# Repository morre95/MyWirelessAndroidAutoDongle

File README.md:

# Wireless Android Auto Dongle

DIY Wireless Android Auto adapter to use with a car that supports only wired Android Auto using a Raspberry Pi.

This repository consists of the buildroot setup to generate an sd card image to create your own Wireless Android Auto adapter.

## Features
- Native Wireless Android Auto connection to the phone, no extra app needed on the phone.
- Passes through all Android Auto traffic without any modifications to ensure seamless and safe experience.
- Fast bootup, connection under 30 seconds.
- Supports multiple boards (Currently multiple Raspberry Pi boards and the Radxa ZERO 3W).

## Supported Hardware
This is currently tested and built for the following boards supporting USB OTG.
- **Raspberry Pi Zero W**
- **Raspberry Pi Zero 2 W**
- **Raspberry Pi 3 A+** _(Raspberry Pi 3 B+ is not supported due to lack of USB OTG support.)_
- **Raspberry Pi 4**
- **Raspberry Pi 5**
- **Radxa ZERO 3W**: only the tested variant (PCB V1.12M, 1 GB RAM, **no eMMC**, AIC8800D80 radio), booting from microSD. Variants with eMMC or another revision are not supported. First released in [v0.2.0](https://github.com/morre95/MyWirelessAndroidAutoDongle/releases/tag/v0.2.0); see [Limitations](#radxa-zero-3w).

In theory, this can be extended to more hardware in future with these basic requirements.

- The board should support USB OTG or Gadget mode.
- Has Wifi and Bluetooth. External should also work if not in-built.
- Should be able to operate on power provided by the car.

## Install and run
[Download a pre-built sd card image](https://github.com/morre95/MyWirelessAndroidAutoDongle/releases) for your board. You can also [build one yourself](BUILDING.md). Install the image on the SD card using your favorite tool.

Release images are named `<board>-sdcard.img.xz`, for example `radxa-zero3w-sdcard.img.xz`. Newer releases also carry a `.sha256` file next to each image. Download both into the same folder and check the image before flashing:

```shell
sha256sum -c radxa-zero3w-sdcard.img.xz.sha256
```

Most imaging tools, such as Raspberry Pi Imager and balenaEtcher, can flash the `.img.xz` file directly. The image is about 386 MB, so any microSD card will fit it. The Radxa ZERO 3W was tested with a 32 GB SanDisk Ultra card.

You may want to update the country code and other settings that works best for you. See [Configurations](#Configurations)

### First-time connection
- Connect the phone to headunit via USB cable, make sure Android Auto starts. Disconnect phone.
- Connect the board to the car. Make sure to use a data cable, with the USB OTG enabled port on the board.
    - On **Raspberry Pi Zero W** and **Raspberry Pi Zero 2 W**: Use the second micro-usb port marked "USB" and not "PWR".
    - On **Raspberry Pi 3 A+**: Use the only USB-A port with an USB-A to USB-A cable.
    - On **Raspberry Pi 4**, use the USB-C port used for normally powering the board.
    - On **Radxa ZERO 3W**: Use USB-C port 1, the USB 2.0 OTG port that also powers the board, with a USB-C to USB-A data cable to the car. The other USB-C port is a USB 3.0 host port and does not power the board.
- Open Bluetooth settings and pair the new device called `AndroidAuto-Dongle-*` or `WirelessAADongle-*` on your phone.
- After this phone should automatically connect via Wifi and the dongle will connect to the headunit via USB and start Android Auto on the car screen.

### Subsequent connections
From the next time, it should automatically connect to the phone and start Android Auto.

Make sure your Bluetooth and Wifi are enabled on the phone.

## Configurations

Once the image is installed on the SD card, you can see the SD card as `WirelessAA` drive.

Edit the `aawgd.conf` file inside the `WirelessAA` drive using a text editor to update the configurations. The file contains the possible configuration options with their explanations.

The Radxa ZERO 3W runs its Wi-Fi access point on 5 GHz (channel 36); the Raspberry Pi boards use 2.4 GHz. Set `AAWG_COUNTRY_CODE` to the country you drive in.

## Troubleshoot

### Common issues

#### Music or audiobook playback stutters

See [the audio troubleshooting guide](AUDIO-TROUBLESHOOTING.md) for a reversible
TCP buffering comparison and instructions for collecting Wi-Fi/USB diagnostics.

#### Bluetooth and Wifi seems connected, but the phone stuck at "Looking for Android Auto"
The most common issue behind this is either bad USB cable or use of wrong USB port on the device. Make sure:
1. The cable is good quality data cable and not power-only cable
2. You're using the OTG enabled usb port on the board, and not the power-only port.

#### "Device not responding" error on headunit
Make sure that "Wireless Android Auto" is enabled in your phone's Andriod Auto settings. This option is only available and required on some older phones.

### Getting logs
Once you've already tried multiple times and it still does not work, you can ssh into the device and try to get some logs.

- Set a static password by setting the `AAWG_WIFI_PASSWORD` config, and enable SSH by setting the `AAWG_ENABLE_SSH` config. See [the instructions to update the configurations](#Configurations).
- Connect the device to the headunit, let it boot and try to connect once. The logs are not persisted across reboots, so you need to get the logs in the same instance soon after you observe the issue.
- Connect to the device using wifi (SSID: AAWirelessDongle, Password: \<as set in the first step>).
- SSH into the device (username: root, password: password, see relevant defconfigs e.g. [raspberrypi0w_defconfig](aa_wireless_dongle/configs/raspberrypi0w_defconfig)).
- Once you're in, try to have a look at `/var/log/messages` file, it should have most relevant logs to start with. You can also copy the file and attach to issues you create if any.

These steps are the same on the Radxa ZERO 3W, whose access point is on 5 GHz.

## Contribute
[Find or create a new issue](https://github.com/morre95/MyWirelessAndroidAutoDongle/issues) for any bugs or improvements.

Feel free to [Create a PR](https://github.com/morre95/MyWirelessAndroidAutoDongle/pulls) to fix any issues. Refer [BUILDING.md](BUILDING.md) for instructions on how to build locally.

## Support 
Please [consider sponsoring](https://github.com/sponsors/nisargjhaveri) if you find the project useful. Even a small donation helps. This will help continuing fixing issues and getting support for more devices and headunit in future.

In any case, don't forget to star on github and spread the word if you think this project might be useful to someone else as well.

## Limitations
This is currently tested with very limited set of headunits and cars. Let me know if it does not work with your headunit.

### Radxa ZERO 3W
The Radxa ZERO 3W has been tested with one board, one phone (Samsung Galaxy S24) and one car head unit. See the [hardware validation record](docs/hardware-validation/radxa-zero3w.md) for the results.
- From a fully switched-off car, Android Auto started in 21–27 seconds over 10 cold starts, including the head unit's own boot. A Raspberry Pi Zero 2 W in the same car took 16–24 seconds. An earlier series had one start at exactly 30 seconds.
- Only the variant listed under [Supported Hardware](#supported-hardware) is tested. Boards with eMMC are not supported.
- A 50-minute session with navigation and music had no disconnects. No logs were reviewed for it.

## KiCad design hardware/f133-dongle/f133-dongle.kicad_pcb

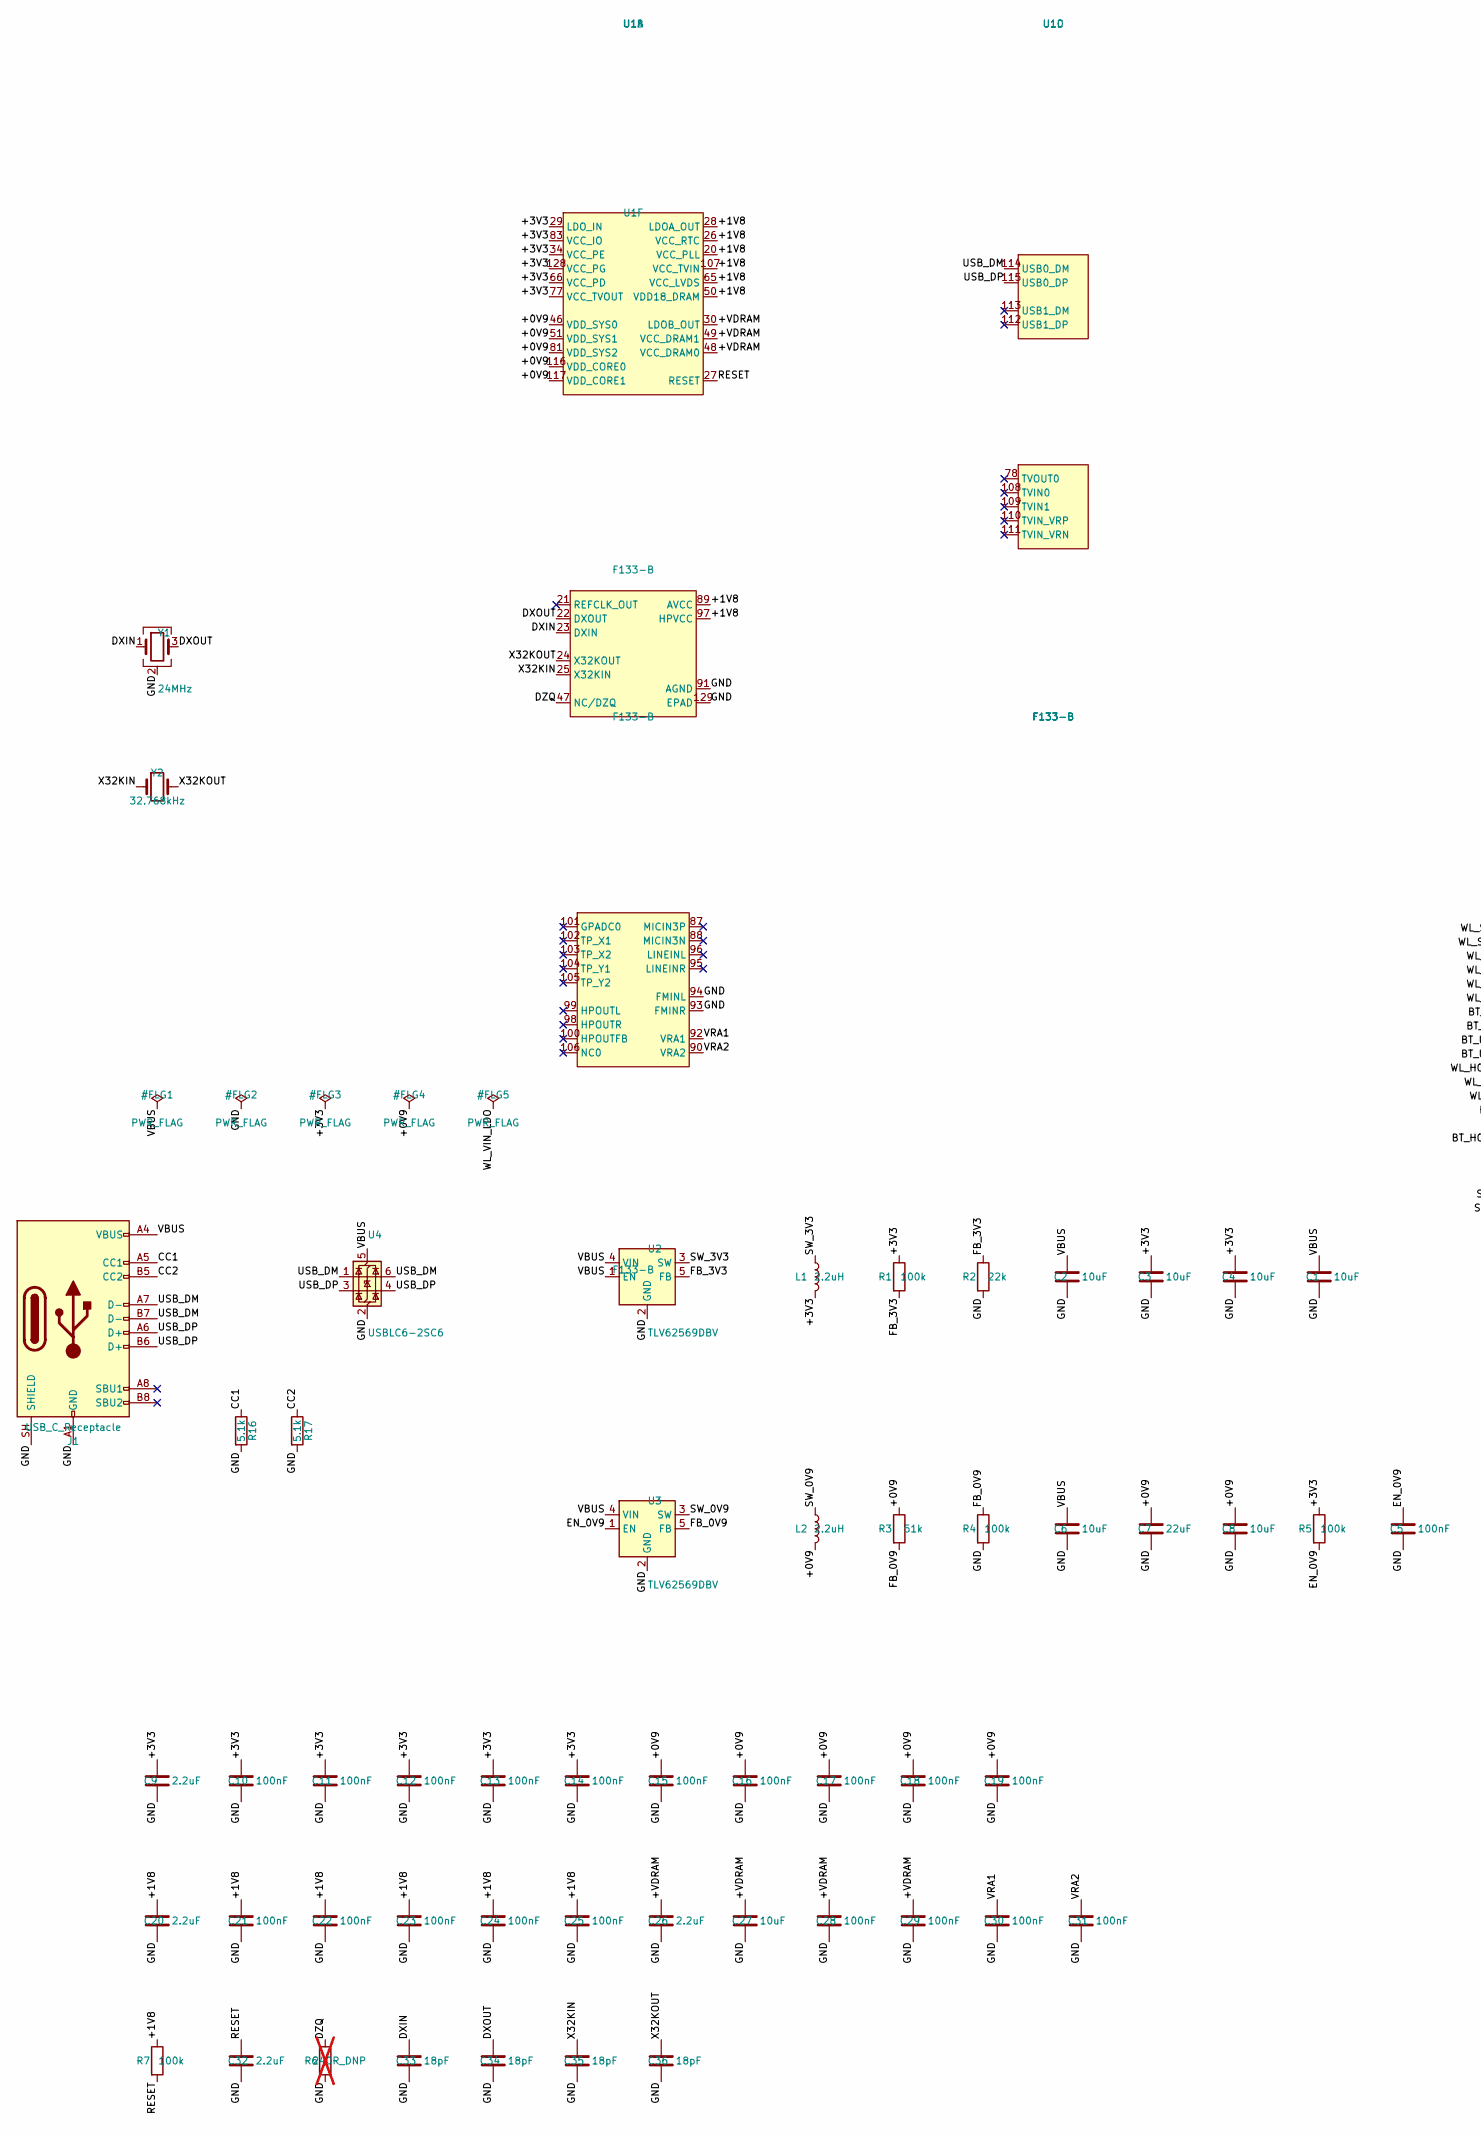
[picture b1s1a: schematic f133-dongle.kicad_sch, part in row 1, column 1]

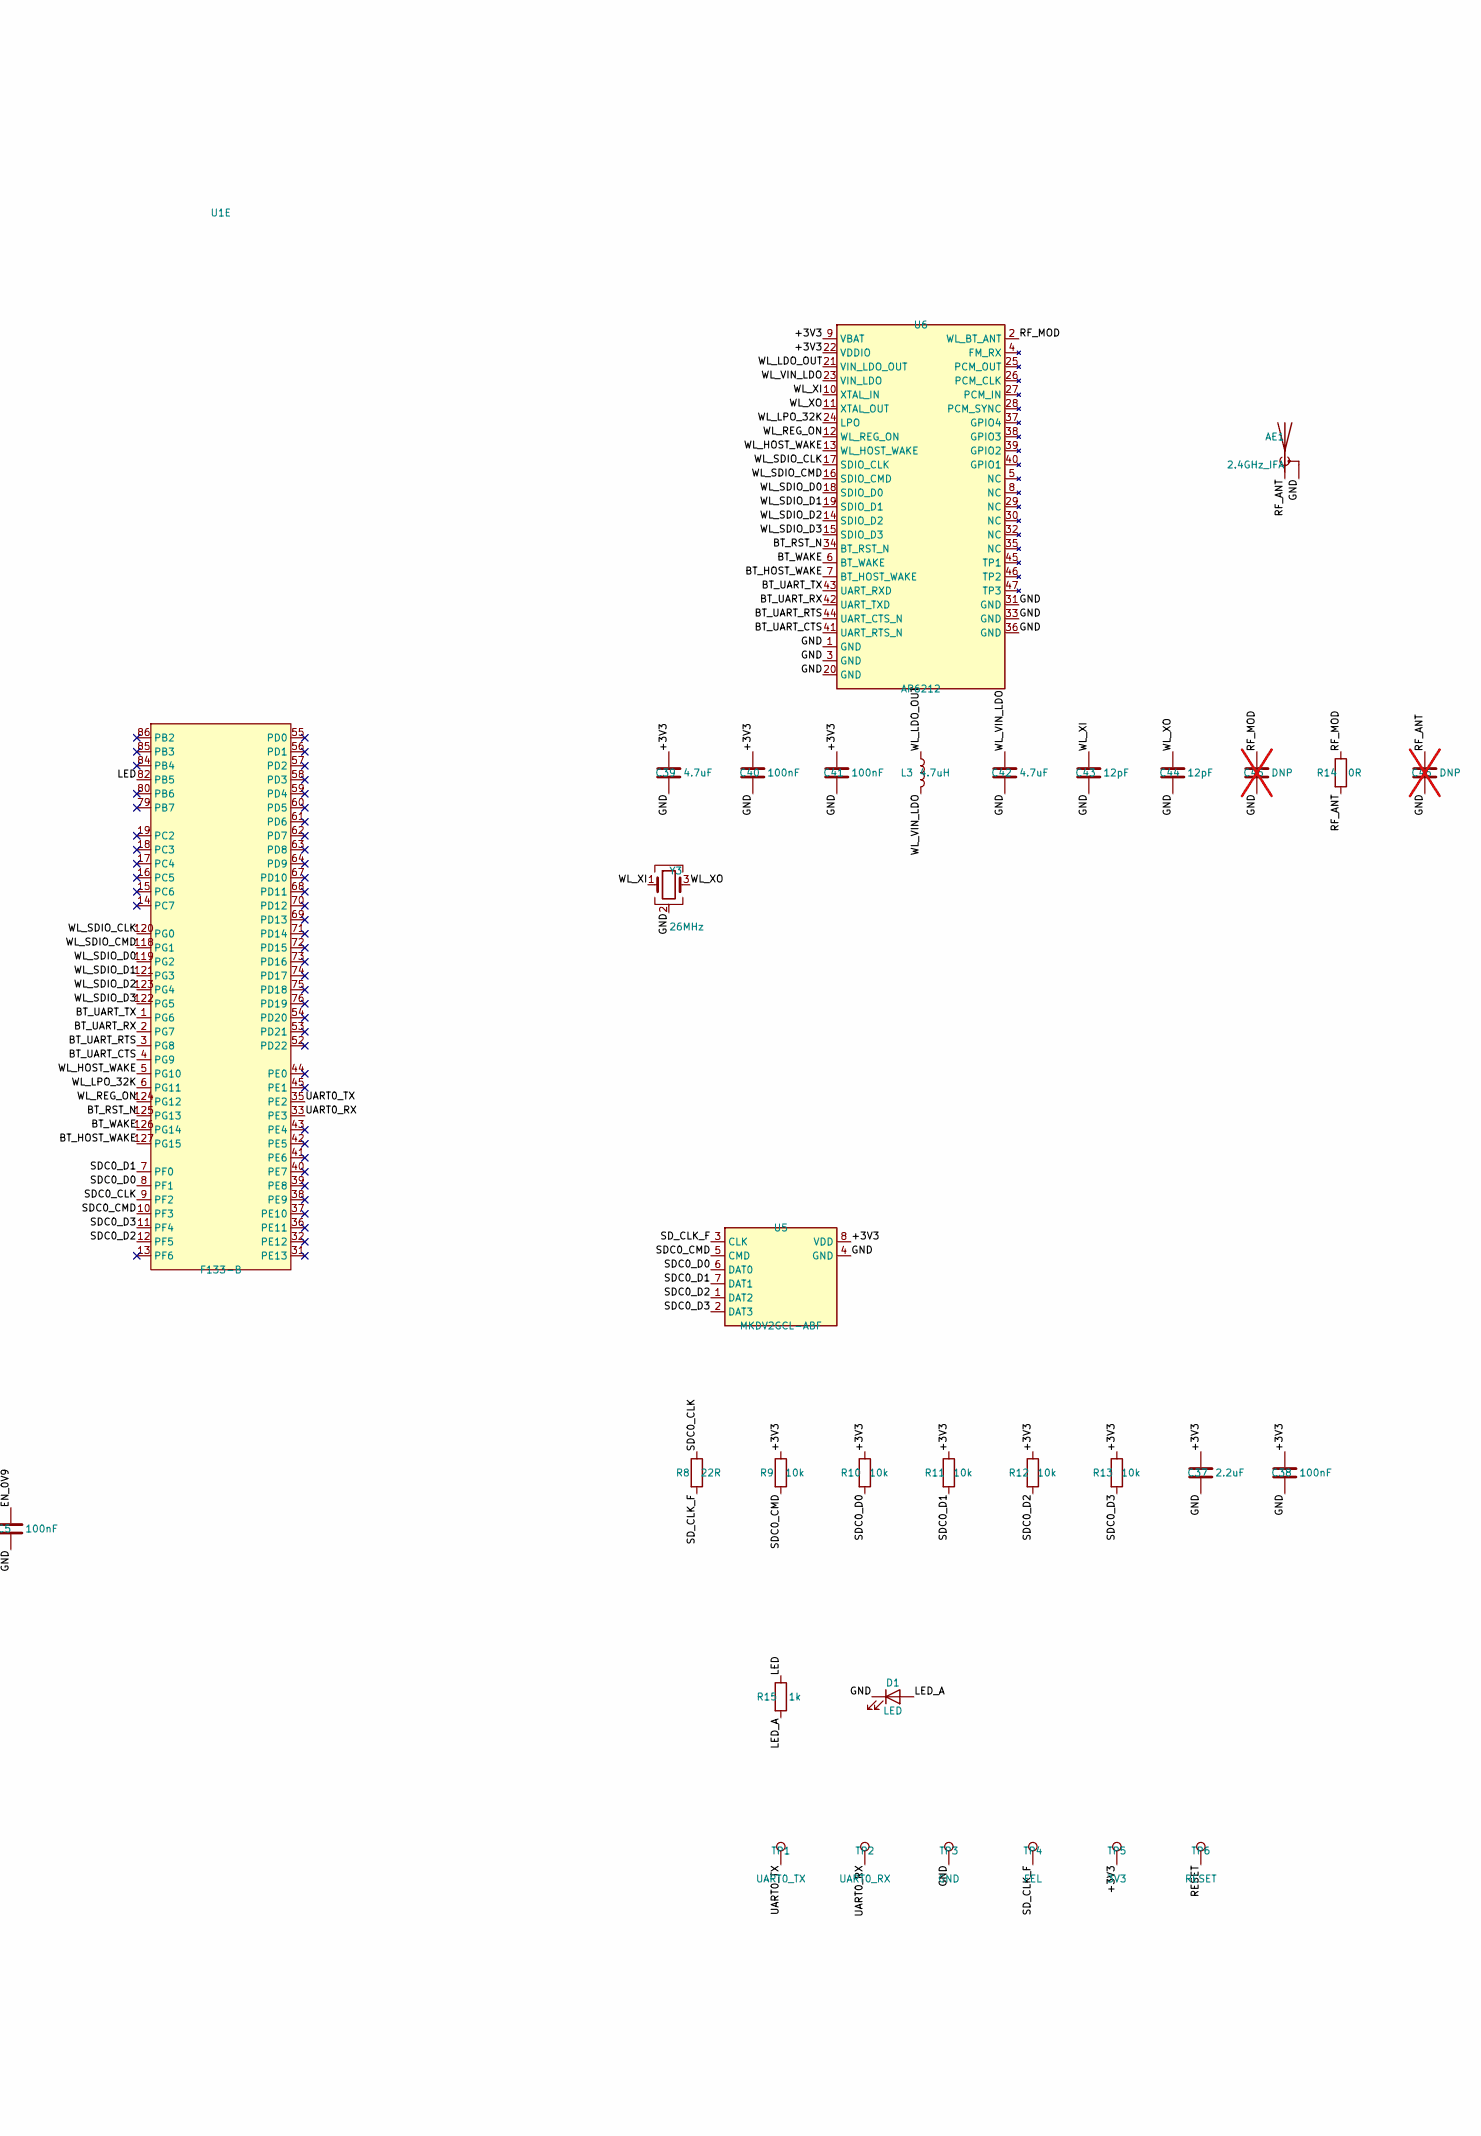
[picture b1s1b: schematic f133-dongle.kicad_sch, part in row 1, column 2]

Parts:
AE1: 2.4GHz_IFA; Texas_SWRA117D_2.4GHz_Left
C1, C2, C3, C4, C6, C8, C27: 10uF; C_0603_1608Metric; LCSC C96446
C5, C10, C11, C12, C13, C14, C15, C16, C17, C18, C19, C21, C22, C23, C24, C25, C28, C29, C30, C31, C38, C40, C41: 100nF; C_0402_1005Metric; LCSC C1525
C7: 22uF; C_0805_2012Metric; LCSC C45783
C9, C20, C26, C32, C37: 2.2uF; C_0402_1005Metric; LCSC C12530
C33, C34, C35, C36: 18pF; C_0402_1005Metric; LCSC C1549
C39, C42: 4.7uF; C_0603_1608Metric; LCSC C19666
C43, C44: 12pF; C_0402_1005Metric; LCSC C1547
C45, C46: DNP; C_0402_1005Metric; not fitted
D1: LED; LED_0603_1608Metric; LCSC C2286
J1: USB_C_Receptacle; USB_C_Receptacle_HRO_TYPE-C-31-M-12; LCSC C165948
L1, L2: 2.2uH; L_1008_2520Metric; LCSC C964122
L3: 4.7uH; L_0805_2012Metric; LCSC C86090
R1, R4, R5, R7: 100k; R_0402_1005Metric; LCSC C25741
R2: 22k; R_0402_1005Metric; LCSC C25768
R3: 51k; R_0402_1005Metric; LCSC C25794
R6: 240R_DNP; R_0402_1005Metric; LCSC C114755; not fitted
R8: 22R; R_0402_1005Metric; LCSC C25092
R9, R10, R11, R12, R13: 10k; R_0402_1005Metric; LCSC C25744
R14: 0R; R_0402_1005Metric; LCSC C17168
R15: 1k; R_0402_1005Metric; LCSC C11702
R16, R17: 5.1k; R_0402_1005Metric; LCSC C25905
TP1: UART0_TX; TestPoint_Pad_D1.0mm
TP2: UART0_RX; TestPoint_Pad_D1.0mm
TP3: GND; TestPoint_Pad_D1.0mm
TP4: FEL; TestPoint_Pad_D1.0mm
TP5: 3V3; TestPoint_Pad_D1.0mm
TP6: RESET; TestPoint_Pad_D1.0mm
U1: F133-B; eLQFP-128_14x14mm_P0.4mm_EP5.72mm; LCSC C22438485
U2, U3: TLV62569DBV; SOT-23-5; LCSC C141836
U4: USBLC6-2SC6; SOT-23-6; LCSC C7519
U5: MKDV2GCL-ABF; LGA-8_8x6mm_P1.27mm_SD_NAND; LCSC C51966231
U6: AP6212; AMPAK_AP62xx_12x12mm
Y1: 24MHz; Crystal_SMD_3225-4Pin_3.2x2.5mm; LCSC C164058
Y2: 32.768kHz; Crystal_SMD_3215-2Pin_3.2x1.5mm; LCSC C32346
Y3: 26MHz; Crystal_SMD_3225-4Pin_3.2x2.5mm; LCSC C15192

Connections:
/+0V9: C7.1, C8.1, C15.1, C16.1, C17.1, C18.1, C19.1, L2.2, R3.1, U1.46 (VDD_SYS0), U1.51 (VDD_SYS1), U1.81 (VDD_SYS2), U1.116 (VDD_CORE0), U1.117 (VDD_CORE1)
/+1V8: C20.1, C21.1, C22.1, C23.1, C24.1, C25.1, R7.1, U1.20 (VCC_PLL), U1.26 (VCC_RTC), U1.28 (LDOA_OUT), U1.50 (VDD18_DRAM), U1.65 (VCC_LVDS), U1.89 (AVCC), U1.97 (HPVCC), U1.107 (VCC_TVIN)
/+3V3: C3.1, C4.1, C9.1, C10.1, C11.1, C12.1, C13.1, C14.1, C37.1, C38.1, C39.1, C40.1, C41.1, L1.2, R1.1, R5.1, R9.1, R10.1, R11.1, R12.1, R13.1, TP5.1, U1.29 (LDO_IN), U1.34 (VCC_PE), U1.66 (VCC_PD), U1.77 (VCC_TVOUT), U1.83 (VCC_IO), U1.128 (VCC_PG), U5.8 (VDD), U6.9 (VBAT), U6.22 (VDDIO)
/+VDRAM: C26.1, C27.1, C28.1, C29.1, U1.30 (LDOB_OUT), U1.48 (VCC_DRAM0), U1.49 (VCC_DRAM1)
/BT_HOST_WAKE: U1.127 (PG15), U6.7 (BT_HOST_WAKE)
/BT_RST_N: U1.125 (PG13), U6.34 (BT_RST_N)
/BT_UART_CTS: U1.4 (PG9), U6.41 (UART_RTS_N)
/BT_UART_RTS: U1.3 (PG8), U6.44 (UART_CTS_N)
/BT_UART_RX: U1.2 (PG7), U6.42 (UART_TXD)
/BT_UART_TX: U1.1 (PG6), U6.43 (UART_RXD)
/BT_WAKE: U1.126 (PG14), U6.6 (BT_WAKE)
/CC1: J1.A5 (CC1), R16.1
/CC2: J1.B5 (CC2), R17.1
/DXIN: C33.1, U1.23 (DXIN), Y1.1
/DXOUT: C34.1, U1.22 (DXOUT), Y1.3
/DZQ: R6.1, U1.47 (NC/DZQ)
/EN_0V9: C5.1, R5.2, U3.1 (EN)
/FB_0V9: R3.2, R4.1, U3.5 (FB)
/FB_3V3: R1.2, R2.1, U2.5 (FB)
/GND: AE1.2 (Shield), C1.2, C2.2, C3.2, C4.2, C5.2, C6.2, C7.2, C8.2, C9.2, C10.2, C11.2, C12.2, C13.2, C14.2, C15.2, C16.2, C17.2, C18.2, C19.2, C20.2, C21.2, C22.2, C23.2, C24.2, C25.2, C26.2, C27.2, C28.2, C29.2, C30.2, C31.2, C32.2, C33.2, C34.2, C35.2, C36.2, C37.2, C38.2, C39.2, C40.2, C41.2, C42.2, C43.2, C44.2, C45.2, C46.2, D1.1 (K), J1.A1 (GND), J1.A12 (GND), J1.B1 (GND), J1.B12 (GND), J1.SH (SHIELD), R2.2, R4.2, R6.2, R16.2, R17.2, TP3.1, U1.91 (AGND), U1.93 (FMINR), U1.94 (FMINL), U1.129 (EPAD), U2.2 (GND), U3.2 (GND), U4.2 (GND), U5.4 (GND), U6.1 (GND), U6.3 (GND), U6.20 (GND), U6.31 (GND), U6.33 (GND), U6.36 (GND), Y1.2 (G), Y1.4 (G), Y3.2 (G), Y3.4 (G)
/LED: R15.1, U1.82 (PB5)
/LED_A: D1.2 (A), R15.2
/RESET: C32.1, R7.2, TP6.1, U1.27 (RESET)
/RF_ANT: AE1.1 (A), C46.1, R14.2
/RF_MOD: C45.1, R14.1, U6.2 (WL_BT_ANT)
/SDC0_CLK: R8.1, U1.9 (PF2)
/SDC0_CMD: R9.2, U1.10 (PF3), U5.5 (CMD)
/SDC0_D0: R10.2, U1.8 (PF1), U5.6 (DAT0)
/SDC0_D1: R11.2, U1.7 (PF0), U5.7 (DAT1)
/SDC0_D2: R12.2, U1.12 (PF5), U5.1 (DAT2)
/SDC0_D3: R13.2, U1.11 (PF4), U5.2 (DAT3)
/SD_CLK_F: R8.2, TP4.1, U5.3 (CLK)
/SW_0V9: L2.1, U3.3 (SW)
/SW_3V3: L1.1, U2.3 (SW)
/UART0_RX: TP2.1, U1.33 (PE3)
/UART0_TX: TP1.1, U1.35 (PE2)
/USB_DM: J1.A7 (D-), J1.B7 (D-), U1.114 (USB0_DM), U4.1 (I/O1), U4.6 (I/O1)
/USB_DP: J1.A6 (D+), J1.B6 (D+), U1.115 (USB0_DP), U4.3 (I/O2), U4.4 (I/O2)
/VBUS: C1.1, C2.1, C6.1, J1.A4 (VBUS), J1.A9 (VBUS), J1.B4 (VBUS), J1.B9 (VBUS), U2.1 (EN), U2.4 (VIN), U3.4 (VIN), U4.5 (VBUS)
/VRA1: C30.1, U1.92 (VRA1)
/VRA2: C31.1, U1.90 (VRA2)
/WL_HOST_WAKE: U1.5 (PG10), U6.13 (WL_HOST_WAKE)
/WL_LDO_OUT: L3.1, U6.21 (VIN_LDO_OUT)
/WL_LPO_32K: U1.6 (PG11), U6.24 (LPO)
/WL_REG_ON: U1.124 (PG12), U6.12 (WL_REG_ON)
/WL_SDIO_CLK: U1.120 (PG0), U6.17 (SDIO_CLK)
/WL_SDIO_CMD: U1.118 (PG1), U6.16 (SDIO_CMD)
/WL_SDIO_D0: U1.119 (PG2), U6.18 (SDIO_D0)
/WL_SDIO_D1: U1.121 (PG3), U6.19 (SDIO_D1)
/WL_SDIO_D2: U1.123 (PG4), U6.14 (SDIO_D2)
/WL_SDIO_D3: U1.122 (PG5), U6.15 (SDIO_D3)
/WL_VIN_LDO: C42.1, L3.2, U6.23 (VIN_LDO)
/WL_XI: C43.1, U6.10 (XTAL_IN), Y3.1
/WL_XO: C44.1, U6.11 (XTAL_OUT), Y3.3
/X32KIN: C35.1, U1.25 (X32KIN), Y2.1
/X32KOUT: C36.1, U1.24 (X32KOUT), Y2.2

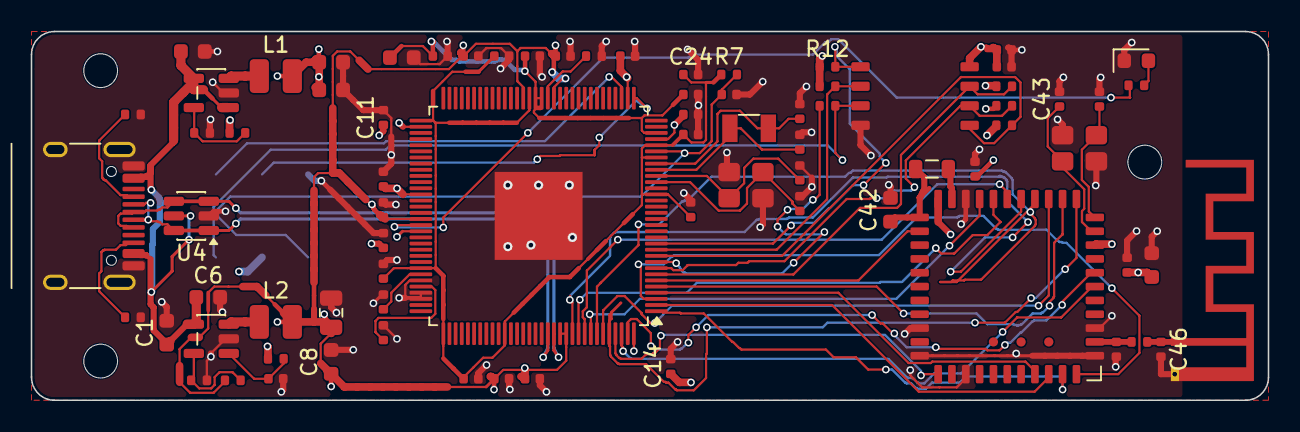
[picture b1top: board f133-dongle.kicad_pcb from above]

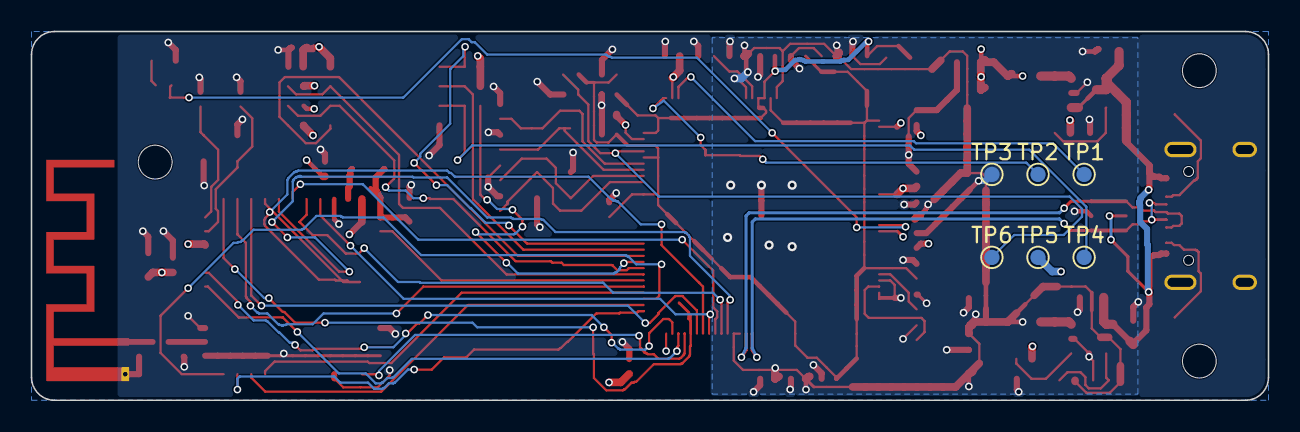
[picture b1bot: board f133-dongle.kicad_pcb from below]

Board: 4 copper layers, 80.5 x 24.0 mm, 87 parts (6 on the bottom side), 56 nets.

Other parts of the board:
H1, H2, H3: MountingHole_2.2mm_NPTH

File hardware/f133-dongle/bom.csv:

Designator,Quantity,Value,Manufacturer,MPN,Description,Footprint,LCSC
"C1, C2, C3, C4, C6, C8, C27",7,10uF,Samsung Electro Mechanics,CL10A106MA8NRNC,10uF 25V X5R ±20% 0603 Multilayer Ceramic Capacitors MLCC - SMD/SMT ROHS,C_0603_1608Metric,C96446
"C5, C10, C11, C12, C13, C14, C15, C16, C17, C18, C19, C21, C22, C23, C24, C25, C28, C29, C30, C31, C38, C40, C41",23,100nF,Samsung Electro Mechanics,CL05B104KO5NNNC,100nF 16V X7R ±10% 0402 Multilayer Ceramic Capacitors MLCC - SMD/SMT ROHS,C_0402_1005Metric,C1525
C7,1,22uF,Samsung Electro Mechanics,CL21A226MAQNNNE,22uF 25V X5R ±20% 0805 Multilayer Ceramic Capacitors MLCC - SMD/SMT ROHS,C_0805_2012Metric,C45783
"C9, C20, C26, C32, C37",5,2.2uF,Samsung Electro Mechanics,CL05A225MQ5NSNC,2.2uF 6.3V X5R ±20% 0402 Multilayer Ceramic Capacitors MLCC - SMD/SMT ROHS,C_0402_1005Metric,C12530
"C33, C34, C35, C36",4,18pF,FH Guangdong Fenghua Advanced Tech,0402CG180J500NT,18pF 50V C0G ±5% 0402 Multilayer Ceramic Capacitors MLCC - SMD/SMT ROHS,C_0402_1005Metric,C1549
"C39, C42",2,4.7uF,Samsung Electro Mechanics,CL10A475KO8NNNC,16V 4.7uF X5R ±10% 0603 Multilayer Ceramic Capacitors MLCC - SMD/SMT ROHS,C_0603_1608Metric,C19666
"C43, C44",2,12pF,FH Guangdong Fenghua Advanced Tech,0402CG120J500NT,12pF 50V C0G ±5% 0402 Multilayer Ceramic Capacitors MLCC - SMD/SMT ROHS,C_0402_1005Metric,C1547
D1,1,LED,Hubei KENTO Elec,KT-0603R,-40℃~+85℃ 1.6mm x 0.8mm square LED 1.8V~2.4V 120° 20mA 300mcd 40mW 615nm~630nm 645nm Discrete Diode Red Water Clear 0603 LED Indication - Discrete ROHS,LED_0603_1608Metric,C2286
J1,1,USB_C_Receptacle,Korean Hroparts Elec,TYPE-C-31-M-12,"-30℃~+80℃ 1 10,000 cycles 16P 20V 5A 7.35mm Female Surface Mount, Right Angle Type-C SMD USB Connectors ROHS",USB_C_Receptacle_HRO_TYPE-C-31-M-12,C165948
"L1, L2",2,2.2uH,INPAQ,WIP252012P-2R2ML,2.06A 2.2uH 2.73A 85mΩ ±20% 1008 Power Inductors ROHS,L_1008_2520Metric,C964122
L3,1,4.7uH,Murata Electronics,LQM21PN4R7MGRD,288mΩ 30MHz 4.7uH 800mA Multilayer inductor ±20% 0805 Inductors (SMD) ROHS,L_0805_2012Metric,C86090
"R1, R4, R5, R7",4,100k,UNI ROYAL Uniroyal Elec,0402WGF1003TCE,-55℃~+155℃ 100kΩ 50V 62.5mW Thick Film Resistor ±1% ±100ppm/℃ 0402 Chip Resistor - Surface Mount ROHS,R_0402_1005Metric,C25741
R2,1,22k,UNI ROYAL Uniroyal Elec,0402WGF2202TCE,-55℃~+155℃ 22kΩ 50V 62.5mW Thick Film Resistor ±1% ±100ppm/℃ 0402 Chip Resistor - Surface Mount ROHS,R_0402_1005Metric,C25768
R3,1,51k,UNI ROYAL Uniroyal Elec,0402WGF5102TCE,-55℃~+155℃ 50V 51kΩ 62.5mW Thick Film Resistor ±1% ±100ppm/℃ 0402 Chip Resistor - Surface Mount ROHS,R_0402_1005Metric,C25794
R8,1,22R,UNI ROYAL Uniroyal Elec,0402WGF220JTCE,-55℃~+155℃ 22Ω 50V 62.5mW Thick Film Resistor ±1% ±100ppm/℃ 0402 Chip Resistor - Surface Mount ROHS,R_0402_1005Metric,C25092
"R9, R10, R11, R12, R13",5,10k,UNI ROYAL Uniroyal Elec,0402WGF1002TCE,-55℃~+155℃ 10kΩ 50V 62.5mW Thick Film Resistor ±1% ±100ppm/℃ 0402 Chip Resistor - Surface Mount ROHS,R_0402_1005Metric,C25744
R14,1,0R,UNI ROYAL Uniroyal Elec,0402WGF0000TCE,-55℃~+155℃ 0Ω 50V 62.5mW Thick Film Resistor ±1% ±800ppm/℃ 0402 Chip Resistor - Surface Mount ROHS,R_0402_1005Metric,C17168
R15,1,1k,UNI ROYAL Uniroyal Elec,0402WGF1001TCE,-55℃~+155℃ 1kΩ 50V 62.5mW Thick Film Resistor ±1% ±100ppm/℃ 0402 Chip Resistor - Surface Mount ROHS,R_0402_1005Metric,C11702
"R16, R17",2,5.1k,UNI ROYAL Uniroyal Elec,0402WGF5101TCE,-55℃~+155℃ 5.1kΩ 50V 62.5mW Thick Film Resistor ±1% ±100ppm/℃ 0402 Chip Resistor - Surface Mount ROHS,R_0402_1005Metric,C25905
U1,1,F133-B,Allwinner Tech,F133-B,ELQFP-128(14x14) Microcontrollers (MCU/MPU/SOC) ROHS,eLQFP-128_14x14mm_P0.4mm_EP5.72mm,C22438485
"U2, U3",2,TLV62569DBV,Texas Instruments,TLV62569DBVR,-40℃~+125℃@(TJ) 1 1.5MHz 2.5V~5.5V 2A 600mV~5.5V Adjustable Buck Buck Built-in Yes SOT-23-5 DC-DC Converters ROHS,SOT-23-5,C141836
U4,1,USBLC6-2SC6,STMicroelectronics,USBLC6-2SC6,-40℃~+125℃ 150nA 17V 2 3.5pF 5.25V 5A 6V ESD IEC 61000-4-2 Unidirectional SOT-23-6L ESD and Surge Protection (TVS/ESD) ROHS,SOT-23-6,C7519
U5,1,MKDV2GCL-ABF,MK Founder,MKDV2GCL-ABF,-25℃~+85℃ 10 Years 2.7V~3.6V 2Gbit 50MHz SD interface LGA-8(6x8) NAND FLASH ROHS,LGA-8_8x6mm_P1.27mm_SD_NAND,C51966231
U6,1,AP6212,AMPAK,AP6212,WiFi 802.11b/g/n + Bluetooth 4.0 SDIO module,AMPAK_AP62xx_12x12mm,
Y1,1,24MHz,Yajingxin,TAXM24M4RFBCCT2T,-40℃~+85℃ 12pF 24MHz 30Ω Crystal Oscillator ±10ppm ±30ppm SMD3225-4P Crystals ROHS,Crystal_SMD_3225-4Pin_3.2x2.5mm,C164058
Y2,1,32.768kHz,Seiko Epson,Q13FC13500004,-40℃~+85℃ 12.5pF 32.768kHz 70kΩ Crystal Oscillator ±20ppm SMD3215-2P Crystals ROHS,Crystal_SMD_3215-2Pin_3.2x1.5mm,C32346
Y3,1,26MHz,YXC Crystal Oscillators,X322526MMB4SI,-40℃~+85℃ 10pF 26MHz 50Ω Crystal Oscillator ±10ppm ±20ppm SMD3225-4P Crystals ROHS,Crystal_SMD_3225-4Pin_3.2x2.5mm,C15192
